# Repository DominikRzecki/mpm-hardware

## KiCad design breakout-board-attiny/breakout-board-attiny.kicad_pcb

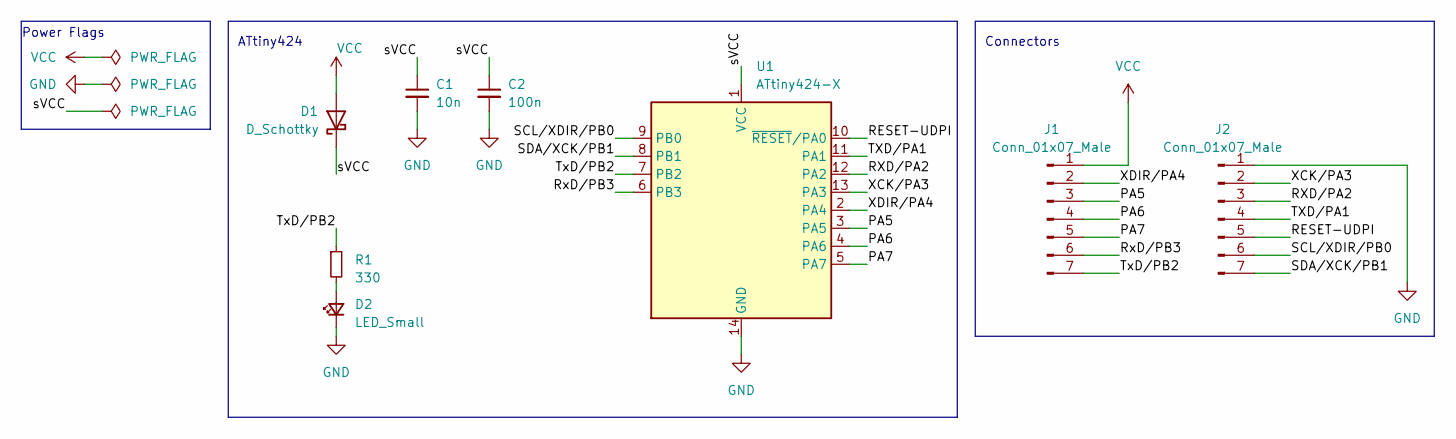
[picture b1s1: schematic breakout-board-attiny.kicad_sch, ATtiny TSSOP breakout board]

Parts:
C1: 10n; C_1206_3216Metric
C2: 100n; C_1206_3216Metric
D1: D_Schottky; D_1206_3216Metric
D2: LED_Small; D_1206_3216Metric
J1, J2: Conn_01x07_Male; PinSocket_1x07_P2.54mm_Vertical
R1: 330; R_1206_3216Metric
U1: ATtiny424-X; TSSOP-14_4.4x5mm_P0.65mm

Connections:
/PA5: J1.3, U1.3 (PA5)
/PA6: J1.4, U1.4 (PA6)
/PA7: J1.5, U1.5 (PA7)
/RESET-UDPI: J2.5, U1.10 (~RESET/PA0)
/RXD/PA2: J2.3, U1.12 (PA2)
/RxD/PB3: J1.6, U1.6 (PB3)
/SCL/XDIR/PB0: J2.6, U1.9 (PB0)
/SDA/XCK/PB1: J2.7, U1.8 (PB1)
/TXD/PA1: J2.4, U1.11 (PA1)
/TxD/PB2: J1.7, R1.1, U1.7 (PB2)
/XCK/PA3: J2.2, U1.13 (PA3)
/XDIR/PA4: J1.2, U1.2 (PA4)
/sVCC: C1.1, C2.1, D1.1 (K), U1.1 (VCC)
GND: C1.2, C2.2, D2.1 (K), J2.1, U1.14 (GND)
unnamed: D2.2 (A), R1.2
VCC: D1.2 (A), J1.1

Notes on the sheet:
Power Flags
Connectors
ATtiny424

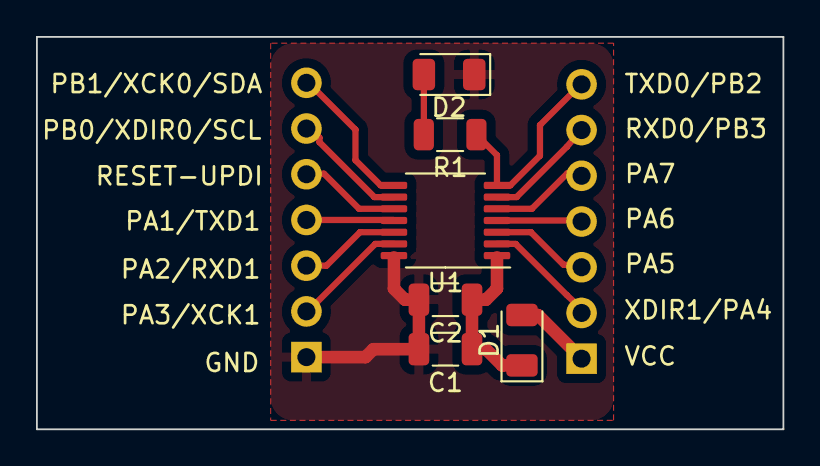
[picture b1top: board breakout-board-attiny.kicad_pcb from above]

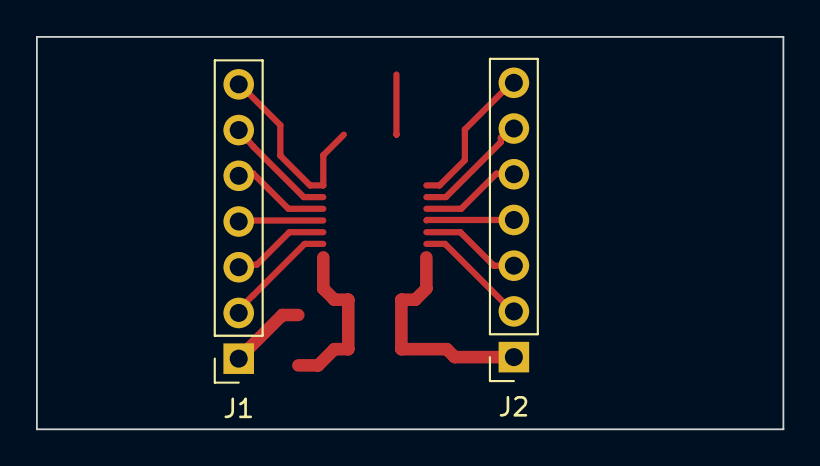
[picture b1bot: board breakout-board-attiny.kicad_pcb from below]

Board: 2 copper layers, 41.5 x 21.8 mm, 8 parts (2 on the bottom side), 16 nets.

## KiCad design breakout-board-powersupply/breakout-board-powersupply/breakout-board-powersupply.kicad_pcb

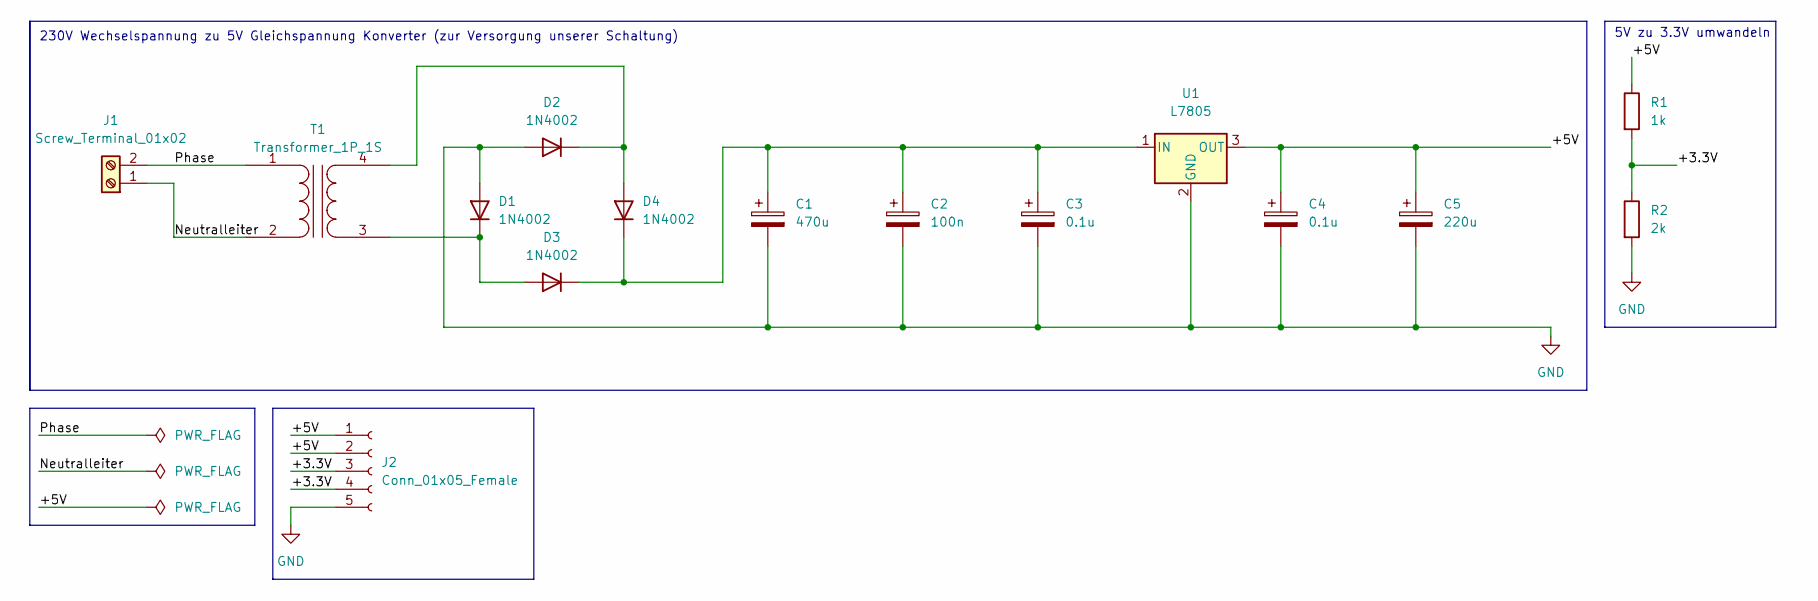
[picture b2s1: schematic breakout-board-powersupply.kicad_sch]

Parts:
C1: 470u; C_1206_3216Metric_Pad1.33x1.80mm_HandSolder
C2: 100n; C_1206_3216Metric_Pad1.33x1.80mm_HandSolder
C3, C4: 0.1u; C_1206_3216Metric_Pad1.33x1.80mm_HandSolder
C5: 220u; C_1206_3216Metric_Pad1.33x1.80mm_HandSolder
D1, D2, D3, D4: 1N4002; D_DO-41_SOD81_P10.16mm_Horizontal
J1: Screw_Terminal_01x02; TerminalBlock_Altech_AK300-2_P5.00mm
J2: Conn_01x05_Female; PinSocket_1x05_P2.54mm_Vertical
R1: 1k; R_1206_3216Metric_Pad1.30x1.75mm_HandSolder
R2: 2k; R_1206_3216Metric_Pad1.30x1.75mm_HandSolder
T1: Transformer_1P_1S
U1: L7805; SOT-223

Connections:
/+3.3V: J2.3, J2.4, R1.2, R2.1
/+5V: C4.1, C5.1, J2.1, J2.2, R1.1, U1.3 (OUT)
/Neutralleiter: J1.1, T1.2 (AB)
/Phase: J1.2, T1.1 (AA)
GND: C1.2, C2.2, C3.2, C4.2, C5.2, D1.2 (A), D2.2 (A), J2.5, R2.2, U1.2 (GND)
unnamed: C1.1, C2.1, C3.1, D3.1 (K), D4.1 (K), U1.1 (IN)
unnamed: D1.1 (K), D3.2 (A), T1.3 (SA)
unnamed: D2.1 (K), D4.2 (A), T1.4 (SB)

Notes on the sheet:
230V Wechselspannung zu 5V Gleichspannung Konverter (zur Versorgung unserer Schaltung)
5V zu 3.3V umwandeln

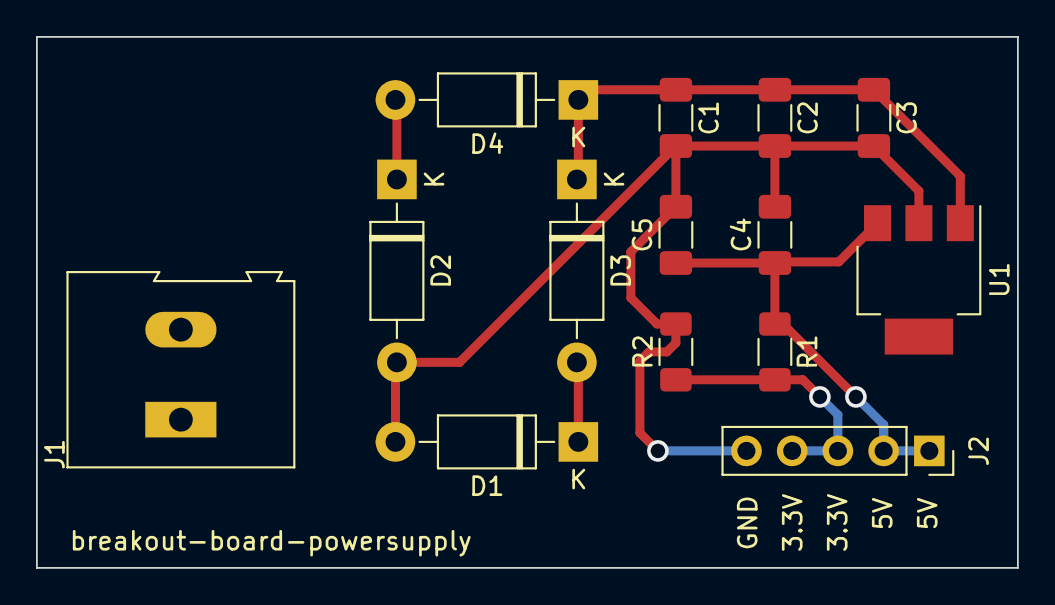
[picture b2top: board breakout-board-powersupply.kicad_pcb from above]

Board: 2 copper layers, 54.5 x 29.5 mm, 14 parts (0 on the bottom side), 6 nets.
